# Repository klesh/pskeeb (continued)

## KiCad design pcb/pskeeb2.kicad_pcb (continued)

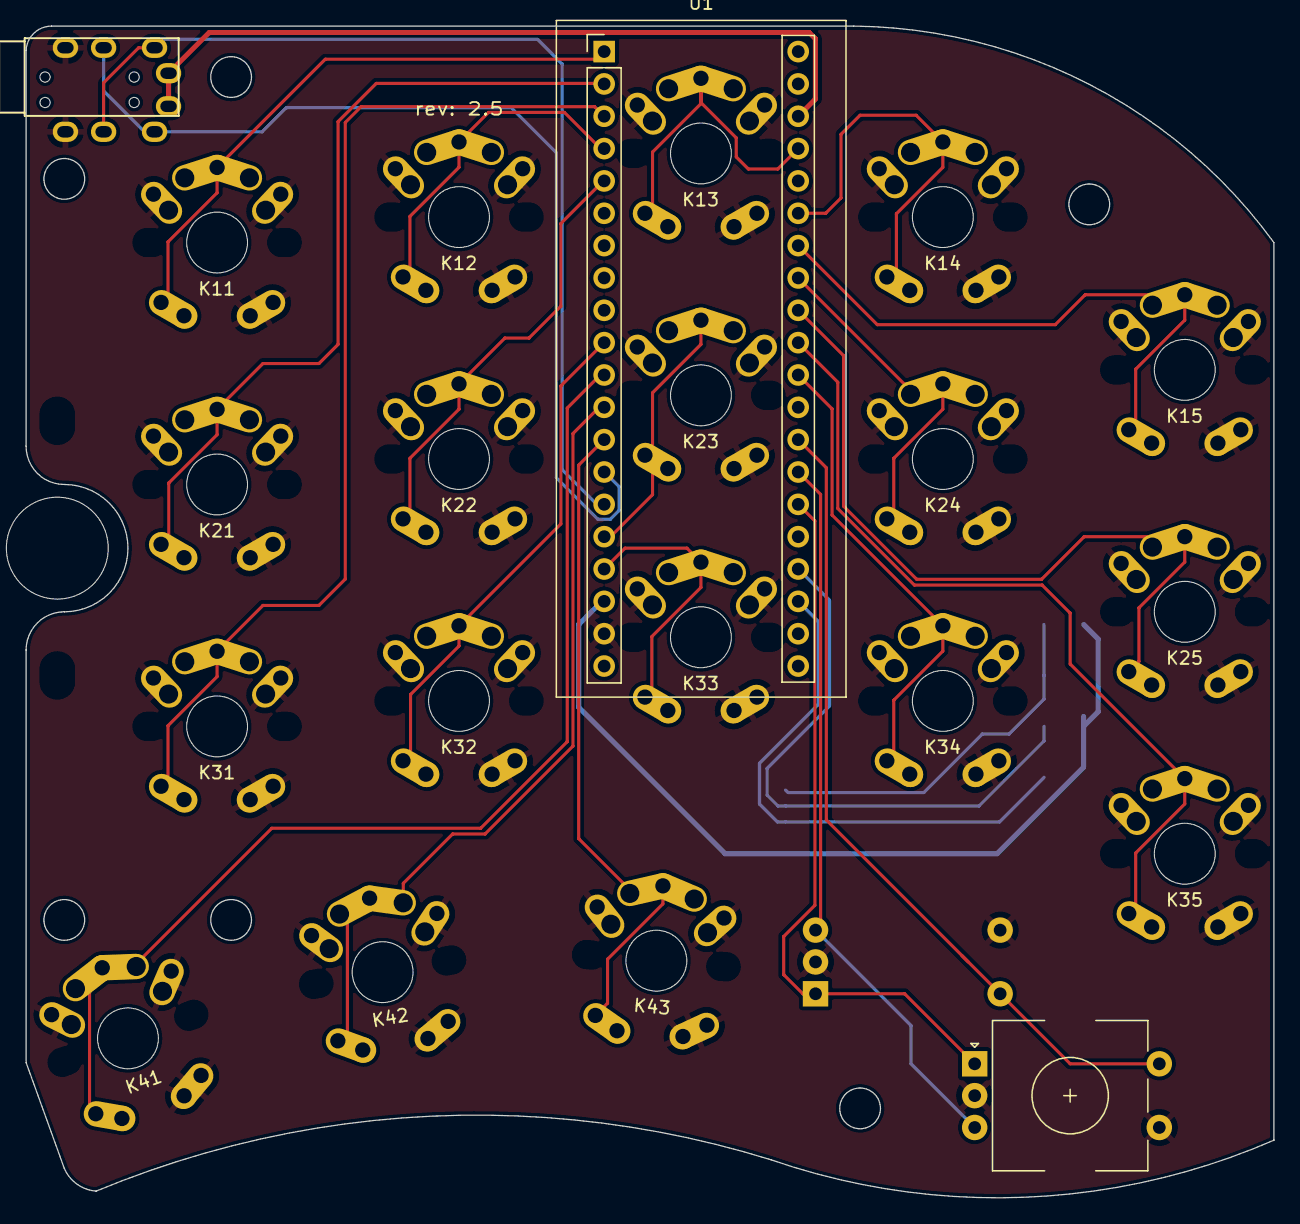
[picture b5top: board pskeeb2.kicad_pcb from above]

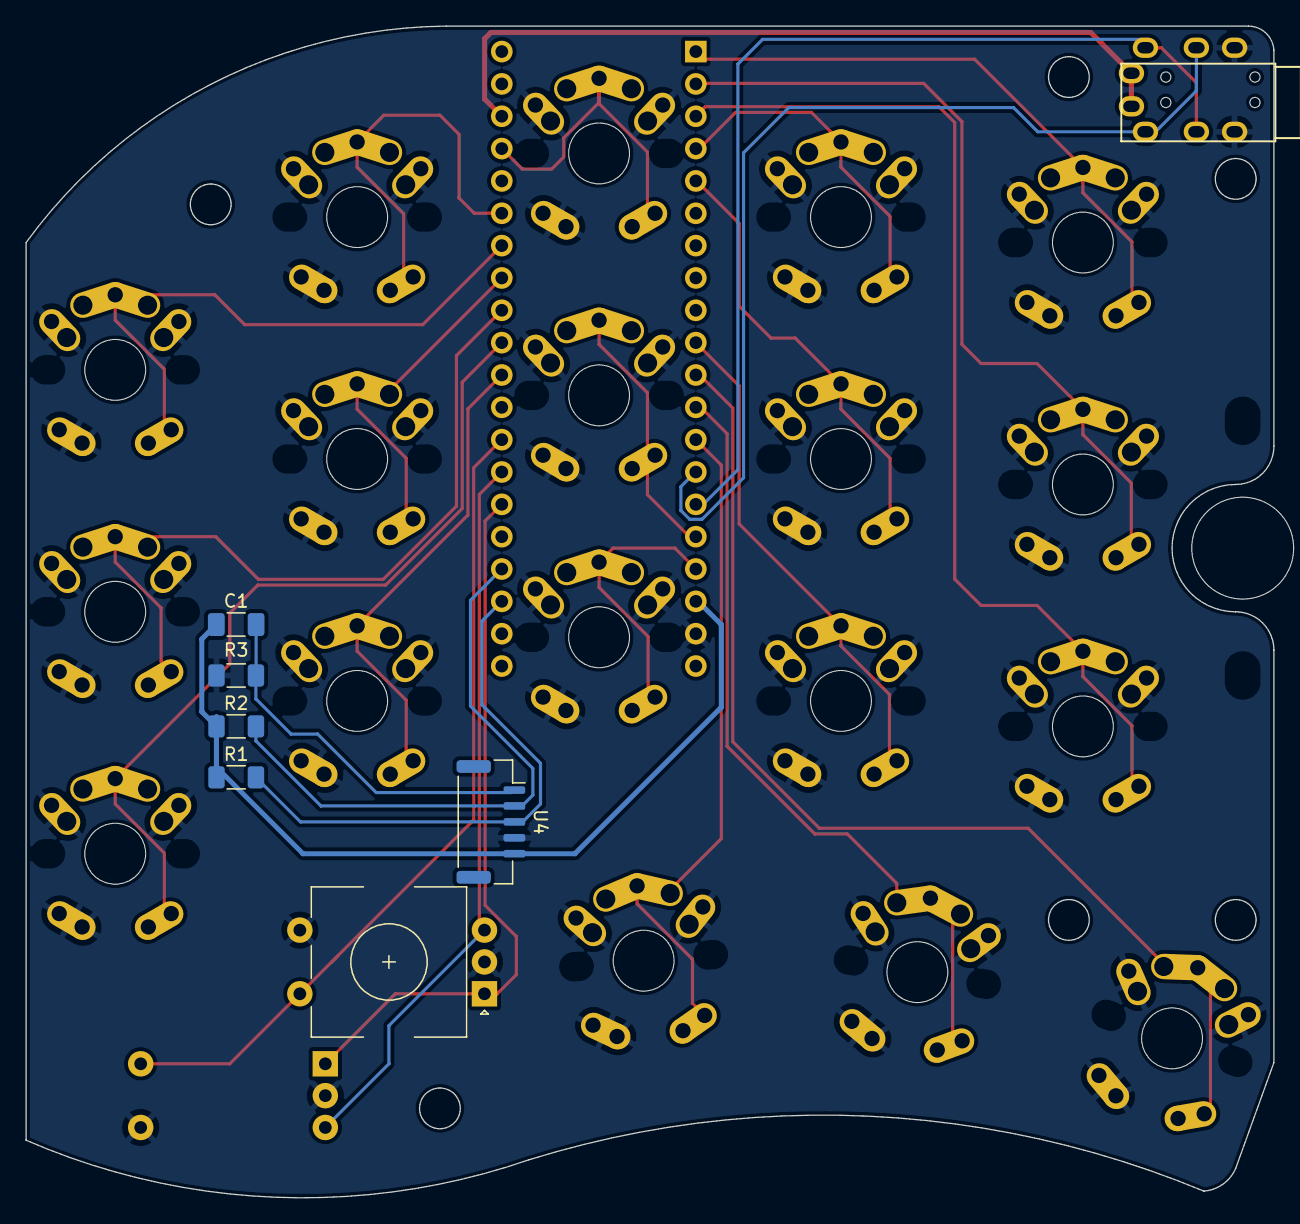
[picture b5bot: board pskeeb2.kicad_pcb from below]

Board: 2 copper layers, 98.0 x 92.0 mm, 29 parts (7 on the bottom side), 29 nets.

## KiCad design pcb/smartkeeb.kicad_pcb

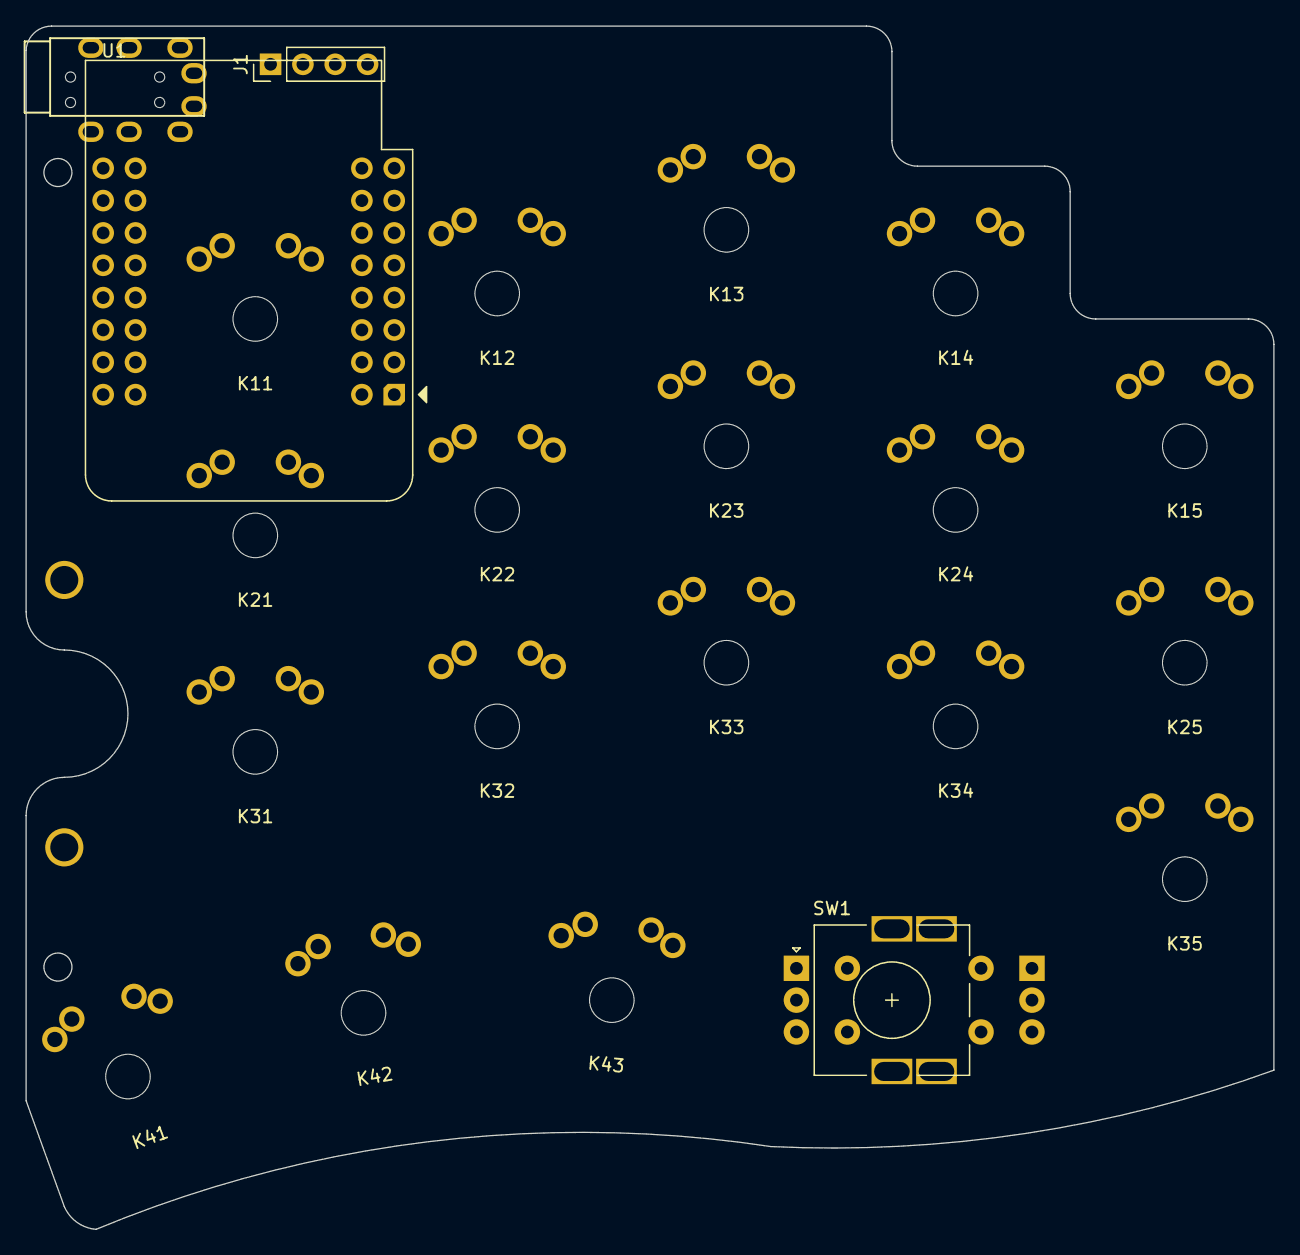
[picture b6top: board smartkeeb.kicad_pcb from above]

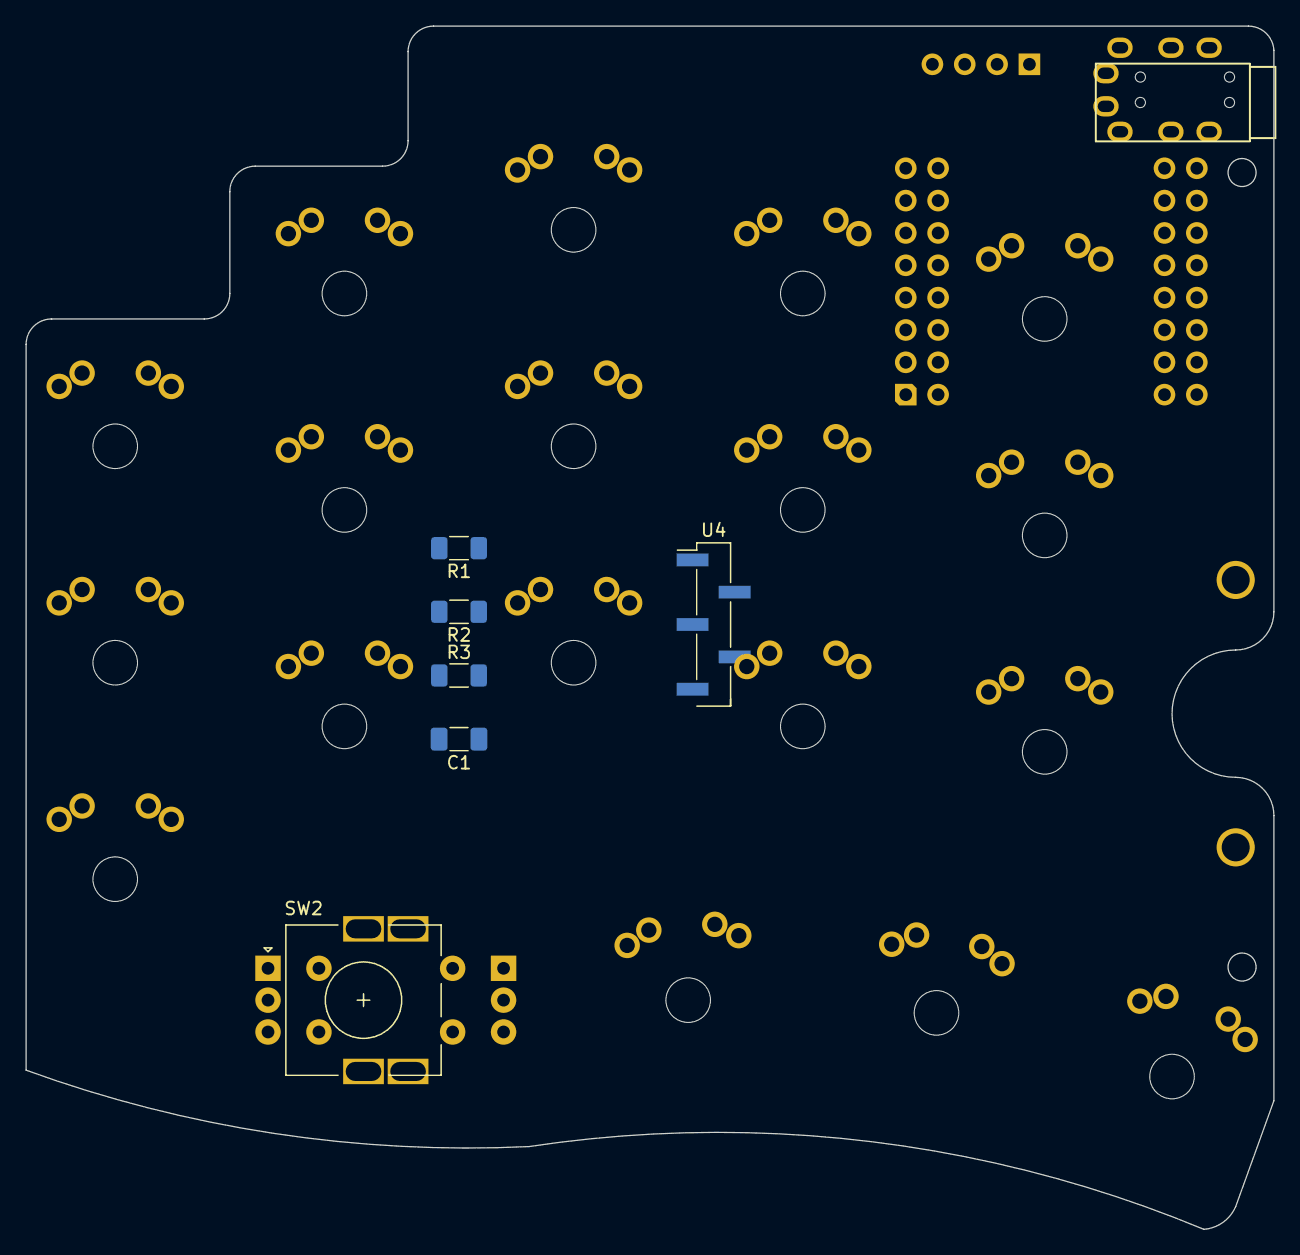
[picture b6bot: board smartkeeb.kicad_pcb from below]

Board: 2 copper layers, 98.0 x 94.5 mm, 29 parts (7 on the bottom side), 9 nets, no tracks yet.

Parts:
C1: 2.2uf; C_1206_3216Metric_Pad1.33x1.80mm_HandSolder
J1: OLED; PinHeader_1x04_P2.54mm_Vertical
K11, K12, K13, K14, K15, K21, K22, K23, K24, K25, K31, K32, K33, K34, K35, K41, K42, K43: KEYSW; Gateron Choc Reversible
R1, R2: 4.7k; R_1206_3216Metric_Pad1.30x1.75mm_HandSolder
R3: 100k; R_1206_3216Metric_Pad1.30x1.75mm_HandSolder
SW1, SW2: RotaryEncoder_Switch; RotaryEncoder_Alps_EC11E-Switch_Vertical_H20mm
U1: wemos-esp32-s2-mini; WEMOS_S2_mini
U2, U3: TRRS; TRRS-PJ-320A
U4: trackpoint; PinHeader_1x05_P2.54mm_Vertical_SMD_Pin1Left

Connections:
+3V3: J1.3, U1.16 (3V3)
+5V: C1.1, R1.1, R2.1, U1.17 (VBUS), U4.5 (VCC)
/k44: SW1.S2, SW2.S2
ENA: SW1.A, SW2.A
ENB: SW1.B, SW2.B
GND: J1.4, K11.1, K12.1, K13.1, K14.1, K15.1, K21.1, K22.1, K23.1, K24.1, K25.1, K31.1, K32.1, K33.1, K34.1, K35.1, K41.1, K42.1, K43.1, R3.2, SW1.C, SW1.S1, SW2.C, SW2.S1, U1.19 (GND), U1.20 (GND), U4.4 (GND)
TP_CLK: R1.2, U4.3 (CLK)
TP_DAT: R2.2, U4.2 (DAT)
TP_RST: C1.2, R3.1, U4.1 (RST)

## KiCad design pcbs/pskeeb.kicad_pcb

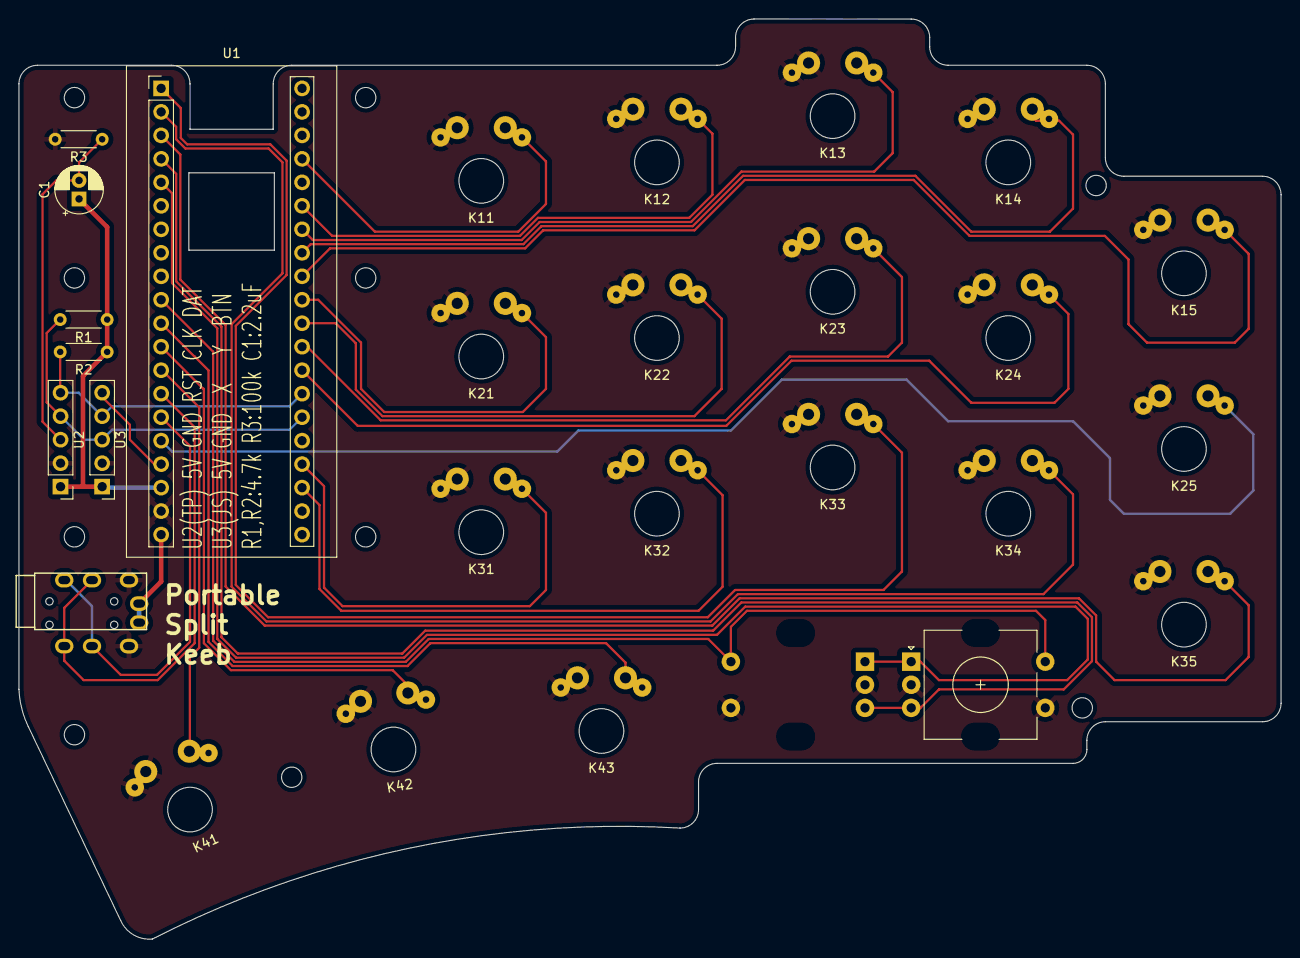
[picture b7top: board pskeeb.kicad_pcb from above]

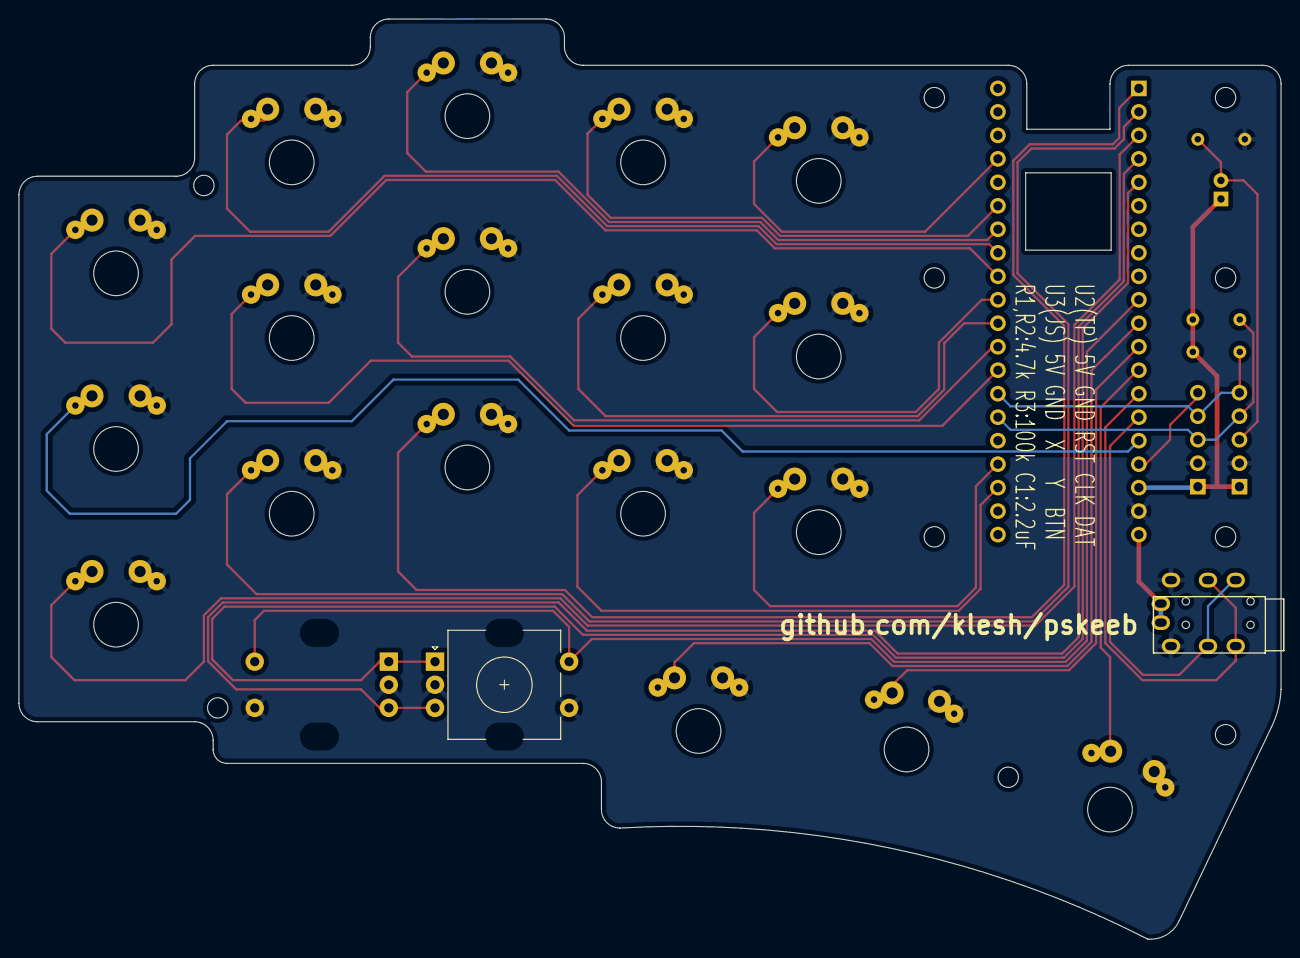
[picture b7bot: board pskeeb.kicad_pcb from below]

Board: 2 copper layers, 136.5 x 99.5 mm, 29 parts (2 on the bottom side), 30 nets.

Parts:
C1: 2.2uf; CP_Radial_D5.0mm_P2.00mm
ENC1, ENC2: RotaryEncoder_Switch; RotaryEncoder_EC11
K11, K12, K13, K14, K15, K21, K22, K23, K24, K25, K31, K32, K33, K34, K35, K41, K42, K43: KEYSW; Gateron KS-27 Reversible
R1, R2: 4.7k; R_Axial_DIN0204_L3.6mm_D1.6mm_P5.08mm_Horizontal
R3: 100k; R_Axial_DIN0204_L3.6mm_D1.6mm_P5.08mm_Horizontal
TRRS1, TRRS2: TRRS; TRRS-PJ-320A
U1: YAAJ_WeAct_BlackPill_Part_Like; YAAJ_WeAct_BlackPill_2
U2: PS/2_Trackpoint; PinHeader_1x05_P2.54mm_Vertical
U3: JoyStick; PinHeader_1x05_P2.54mm_Vertical

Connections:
+3V3: TRRS1.1 (SLEEVE), TRRS2.1 (SLEEVE), U1.20 (3V3)
+5V: C1.1, R1.1, R2.1, U1.18 (5V), U2.1 (VCC), U3.1 (VCC)
/RX: TRRS1.3 (RING1), TRRS2.4 (RING2), U1.15 (PB7)
/TX: TRRS1.4 (RING2), TRRS2.3 (RING1), U1.14 (PB6)
/ec11a: ENC1.A, ENC2.A, U1.5 (PA8)
/ec11b: ENC1.B, ENC2.B, U1.4 (PB15)
/joystick_btn: U1.17 (PB9), U3.5 (BTN)
/joystick_x: R1.2, U1.26 (PA0), U2.4 (CLK), U3.3 (X)
/joystick_y: R2.2, U1.27 (PA1), U2.5 (DAT), U3.4 (Y)
/k11: K11.2, U1.37 (PB10)
/k12: K12.2, U1.35 (PB1)
/k13: K13.2, U1.34 (PB0)
/k14: K14.2, U1.33 (PA7)
/k15: K15.2, U1.32 (PA6)
/k21: K21.2, U1.31 (PA5)
/k22: K22.2, U1.30 (PA4)
/k23: K23.2, U1.29 (PA3)
/k24: K24.2, U1.28 (PA2)
/k25: K25.2, U1.16 (PB8)
/k31: K31.2, U1.24 (PC15)
/k32: K32.2, U1.23 (PC14)
/k33: K33.2, U1.1 (PB12)
/k34: K34.2, U1.2 (PB13)
/k35: K35.2, U1.3 (PB14)
/k41: K41.2, U1.13 (PB5)
/k42: K42.2, U1.12 (PB4)
/k43: K43.2, U1.11 (PB3)
/k44: ENC1.S2, ENC2.S2, U1.10 (PA15)
GND: ENC1.C, ENC1.S1, ENC2.C, ENC2.S1, K11.1, K12.1, K13.1, K14.1, K15.1, K21.1, K22.1, K23.1, K24.1, K25.1, K31.1, K32.1, K33.1, K34.1, K35.1, K41.1, K42.1, K43.1, R3.2, TRRS1.2 (TIP), TRRS2.2 (TIP), U1.19 (GND), U2.2 (GND), U3.2 (GND)
unnamed: C1.2, R3.1, U2.3 (RST)

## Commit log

2022-10-07 feat: first production
2022-10-09 feat: added plates
2022-10-15 refactor: clean up plates
2022-10-15 fix: bigger resistor / ec11 share holes / usb fit
2022-12-03 feat: add kicad source files
2022-12-03 fix: rename files
2022-12-03 feat: finish design
2022-12-03 chore: update lib
2022-12-03 chore: export gerber
2022-12-07 feat: shipped to factory for the pilot
2022-12-08 fix: trrs tx did not connect
2023-01-01 fix: switch courtyard too small / trackpoint mounting
2023-01-09 feat: pskeeb2.1
2023-01-25 fix: leave more space for soldering / use gh1.25 socket for trackpoint
2023-03-12 chore: rev 2.4
2023-03-14 feat: releasing 2.5
2023-03-15 docs: update bom and trackpoint pinout
2023-09-24 feat: organize folders for new boards
2023-09-24 refactor: rename to shorter form
2023-10-04 feat: cherry hotswap shipped to jlc
2023-10-04 chore: update kwkb-kicad
2023-10-10 refactor: rename all designs for a cleaner convention
2023-10-10 typo: rename title
2023-10-19 fix: update plates
2023-10-31 fix: typo slit -> split
2024-01-12 fix: update top plate cut
2024-03-16 feat: added qrcode placeholder
2024-08-29 feat: add pskeeb
2024-11-14 feat: added hugebug trackball
2025-01-10 refactor: increase footprint pads for easier soldering
2025-02-06 feat: added trackball ultimate_ergo
2025-12-29 feat: add license
